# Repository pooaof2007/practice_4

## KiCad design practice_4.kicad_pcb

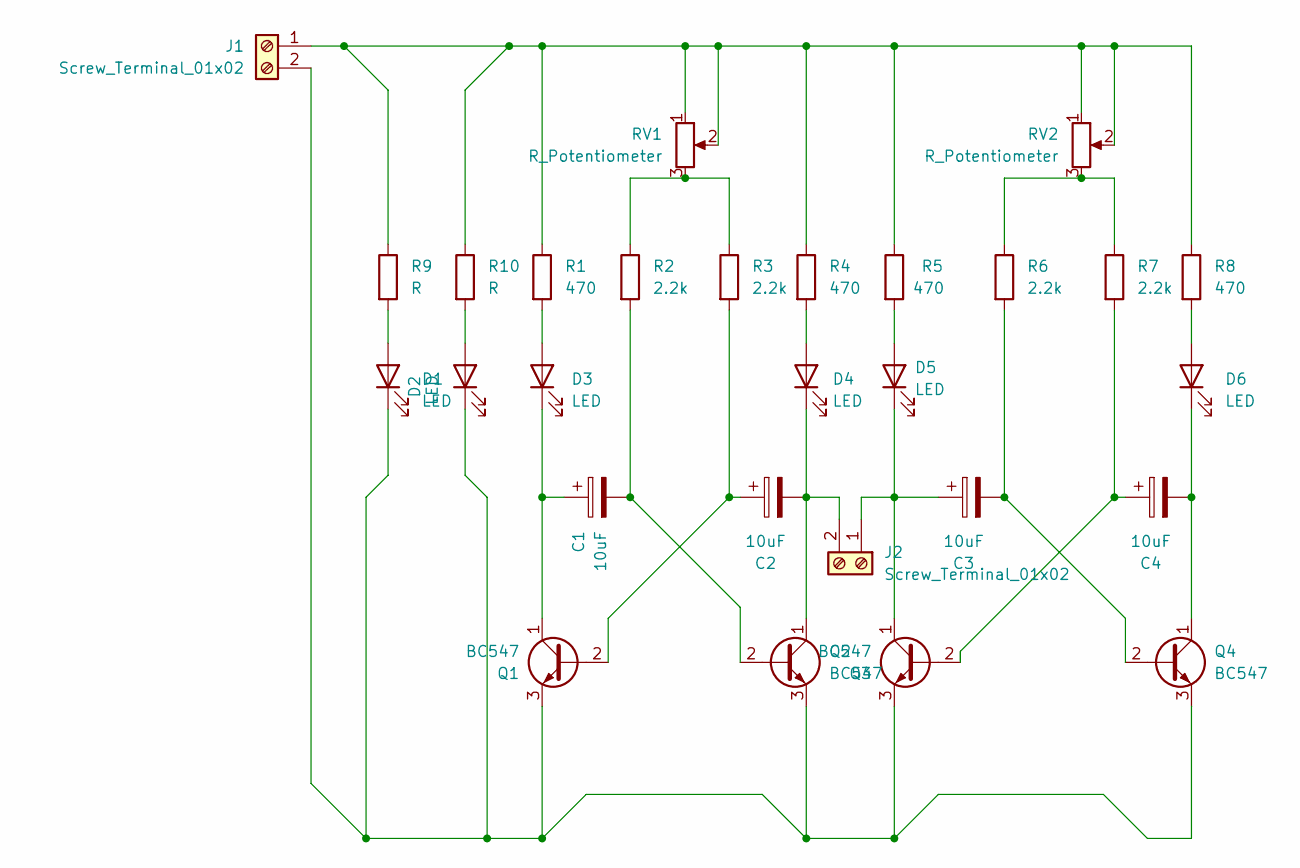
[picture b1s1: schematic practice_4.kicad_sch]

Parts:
C1, C2, C3, C4: 10uF; CP_Radial_D5.0mm_P2.50mm
D1, D2, D3, D4, D5, D6: LED; LED_D3.0mm
J1, J2: Screw_Terminal_01x02; TerminalBlock_MaiXu_MX126-5.0-02P_1x02_P5.00mm
Q1, Q2, Q3, Q4: BC547; TO-92_Inline_Wide
R1, R4, R5, R8: 470; R_Axial_DIN0207_L6.3mm_D2.5mm_P10.16mm_Horizontal
R2, R3, R6, R7: 2.2k; R_Axial_DIN0207_L6.3mm_D2.5mm_P10.16mm_Horizontal
R9, R10: R; R_Axial_DIN0207_L6.3mm_D2.5mm_P10.16mm_Horizontal
RV1, RV2: R_Potentiometer; Potentiometer_Runtron_RM-065_Vertical

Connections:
unnamed: D1.2 (A), R9.2
unnamed: D1.1 (K), D2.1 (K), J1.2, Q1.3 (E), Q2.3 (E), Q3.3 (E), Q4.3 (E)
unnamed: D2.2 (A), R10.2
unnamed: D3.2 (A), R1.2
unnamed: C1.1, D3.1 (K), Q1.1 (C)
unnamed: D4.2 (A), R4.2
unnamed: C2.2, D4.1 (K), J2.2, Q2.1 (C)
unnamed: D5.2 (A), R5.2
unnamed: C3.1, D5.1 (K), J2.1, Q3.1 (C)
unnamed: D6.2 (A), R8.2
unnamed: C4.2, D6.1 (K), Q4.1 (C)
unnamed: J1.1, R1.1, R4.1, R5.1, R8.1, R9.1, R10.1, RV1.1, RV1.2, RV2.1, RV2.2
unnamed: C2.1, Q1.2 (B), R3.2
unnamed: C1.2, Q2.2 (B), R2.2
unnamed: C4.1, Q3.2 (B), R7.2
unnamed: C3.2, Q4.2 (B), R6.2
unnamed: R2.1, R3.1, RV1.3
unnamed: R6.1, R7.1, RV2.3

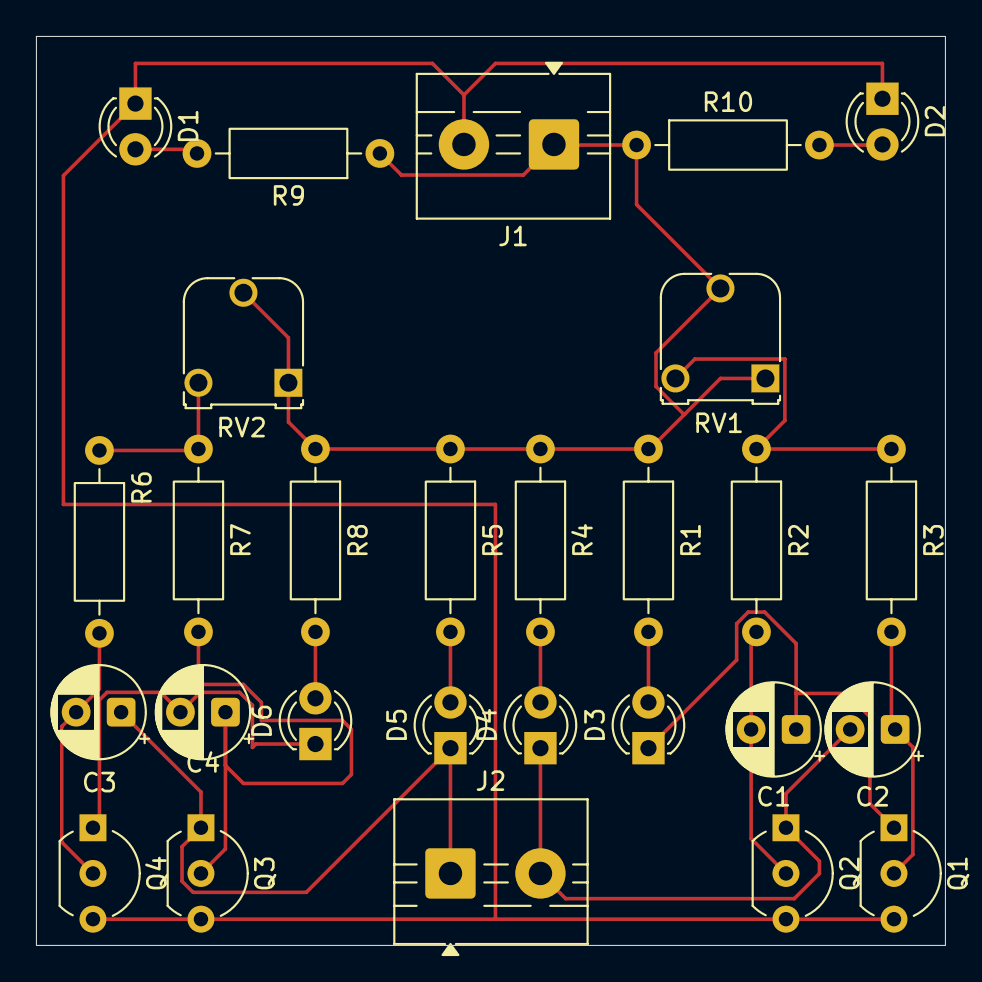
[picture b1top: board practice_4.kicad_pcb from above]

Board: 2 copper layers, 50.5 x 50.5 mm, 28 parts (0 on the bottom side), 18 nets.
